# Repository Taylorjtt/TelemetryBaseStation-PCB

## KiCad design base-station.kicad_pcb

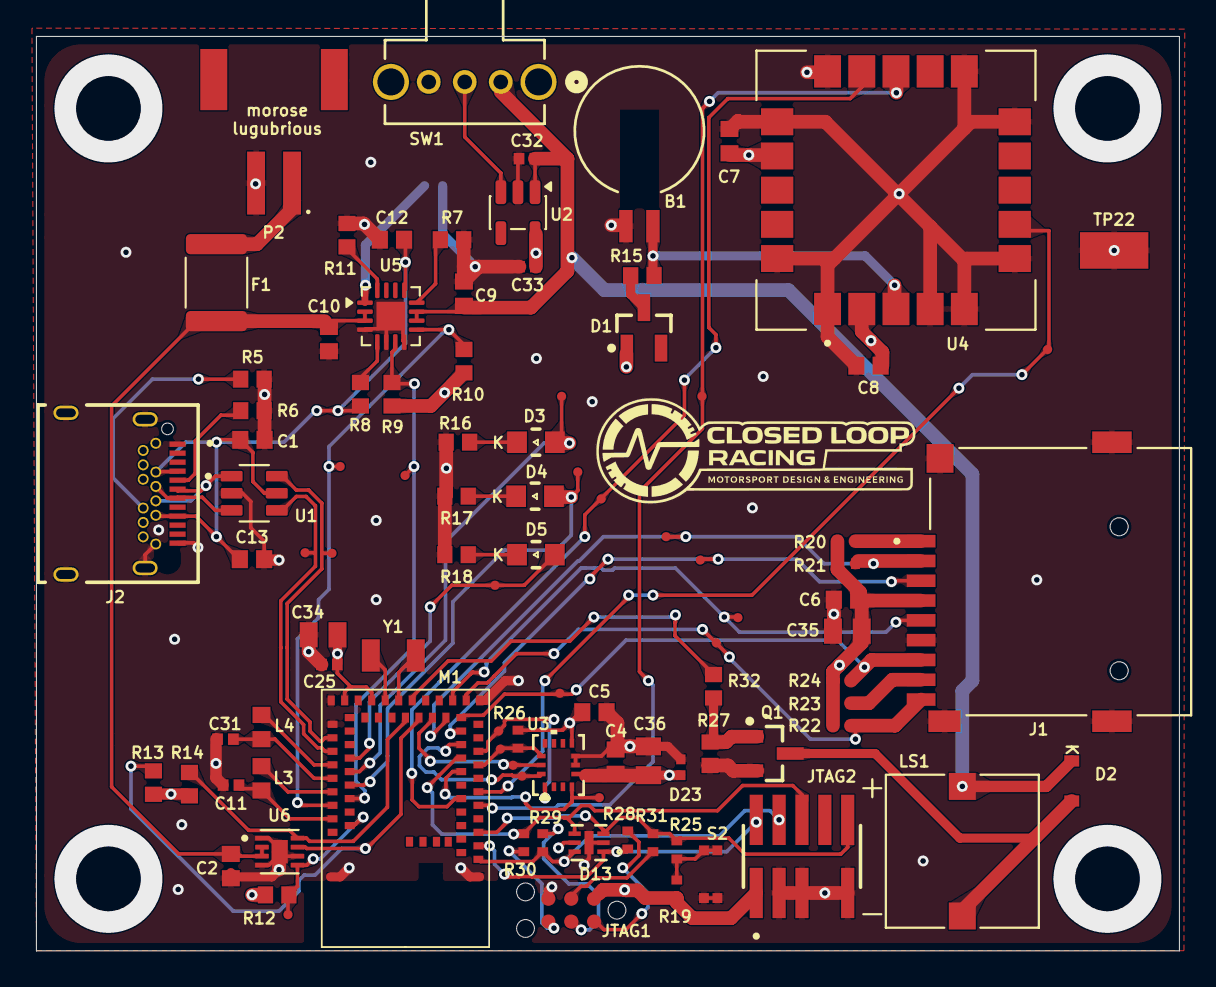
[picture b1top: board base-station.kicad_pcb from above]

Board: 4 copper layers, 63.5 x 50.8 mm, 98 parts (1 on the bottom side), 63 nets.

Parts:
B1: MS621FE-FL11E
C1, C2, C4, C5, C6, C7, C8, C13: 100nF; CAP 0603_1608
C9, C10, C12: 4.7uF; CAP 0603_1608
C11, C25, C31, C32, C33: 1uF; CAP 0402_1005
C34, C35, C36: 10uF; CAP 0805_2012
D1: SOT-23
D2: SOD323
D3: LED_0805_RED
D4: LED_0805_GREEN
D5: LED_0805_YELLOW
D13: SON6_DRTR5V0U4LP16-7_DIO
D23: DIODE 0402_1006
F1: Fuse_1812_4532Metric
J1: CUI_MSD-1-A
J2: GCT_USB4056-03-A_REVA2
JTAG1: TAG_CONNECT
JTAG2: SAMTEC_FTSH-105-01-L-DV-007-K
L3, L4: 10uH; IND 0603_1608
LS1: XDCR_SMT-0827-SW-3V-R
M1: MDBT53
P2: JST_S2B-PH-SM4-TB
Q1: SOT-23
R5, R6: 5.1k; RES 0603_1608
R7, R15, R16, R17, R18, R32: 1.1k; RES 0603_1608
R8, R9, R10, R12, R27: 100k; RES 0603_1608
R11: 887; RES 0603_1608
R13, R14: 4.7K; RES 0603_1608
R19, R20, R21, R22, R23, R24, R26: 10k; RES 0402_1005
R25, R28, R29, R30, R31: 150; RES 0402_1005
RT1: RES 0402_1005
S2: R-668048
SW1: OS102011MA1QN1_CNK
TP1, TP2, TP3, TP4, TP5, TP6, TP7, TP8, TP9, TP10, TP11, TP12, TP13, TP14, TP15, TP16, TP17, TP18, TP19, TP20, TP21: Testpoint_40mil
TP22: Testpoint
U1: SOT-23-6
U2: SOT-23-5
U3: BMI270_BOS
U4: XCVR_SAM-M10Q-00B
U5: VQFN-16-1EP_3x3mm_P0.5mm_EP1.6x1.6mm
U6: SON50P200X200X80-9N
Y1: 32.768 kHz; FC-135

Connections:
3.3V: C4.1, C5.1, C6.1, C7.1, C8.1, C25.1, C33.1, C34.1, C35.1, C36.2, D1.1 (A), D13.5, D23.1, J1.4 (VDD), JTAG1.1, JTAG2.01, M1.38 (VDD), M1.41 (VDDH), R9.1, R10.1, R12.1, R13.1, R14.1, R19.1, R20.1, R21.1, R22.1, R23.1, R24.1, R26.1, U2.5 (VOUT), U3.5 (VDDIO), U3.8 (VDD), U4.2 (V_IO), U4.17 (VCC)
+BATT: C2.1, C10.1, F1.1, U5.2 (BAT), U5.3 (BAT), U6.2 (CELL), U6.3 (VDD)
/ALERT: M1.59 (P1.10), R12.2, TP21.1 (1_1), U6.5 (~ALERT)
/BMI_CS: M1.16 (P0.18/QSPI_CSN), R26.2, TP5.1 (1_1), U3.12 (CSB)
/BMI_MISO: M1.18 (P0.10/HSPI_MISO), TP6.1 (1_1), U3.1 (SDO)
/BMI_MOSI: M1.19 (P0.09/HSPI_MOSI), TP7.1 (1_1), U3.14 (SDX)
/BMI_SCK: M1.29 (P0.08/HSPI_SCK), TP13.1 (1_1), U3.13 (SCX)
/BUZZER: M1.32 (P0.02/NFC1), R32.1
/CARD_DETECT: J1.CD, M1.25 (P0.22), R22.2, TP10.1 (1_1)
/CHG: M1.56 (P0.31), R10.2, TP20.1 (1_1), U5.9 (~CHG)
/D+: M1.46 (D+), TP14.1 (1_1), U1.6
/D-: M1.48 (D-), TP15.1 (1_1), U1.4
/Din+: J2.A6 (DP1), J2.B6 (DP2), U1.1
/Din-: J2.A7 (DN1), J2.B7 (DN2), U1.3
/GPS_LOCK: D3.2, M1.51 (P1.13), TP17.1 (1_1)
/INT1: M1.15 (P0.12/HSPI_DCX), TP4.1 (1_1), U3.4 (INT1)
/PGOOD: M1.55 (P1.11), R9.2, TP19.1 (1_1), U5.7 (~PGOOD)
/RADIO_LINK: D5.2, M1.49 (P1.14), TP16.1 (1_1)
/RECORD: D4.2, M1.53 (P1.12), TP18.1 (1_1)
/RESET: D13.3, JTAG2.10, M1.6 (~RESET), R25.2, R31.1
/SCL: M1.31 (P1.03/TWI), R13.2, U6.7 (SCL)
/SDA: M1.33 (P1.02/TWI), R14.2, U6.8 (SDA)
/SD_CLK: J1.5 (CLK), M1.26 (P0.17/QSPI_SCK), TP11.1 (1_1)
/SD_CS: J1.2 (CD/DAT3), M1.27 (P0.14/QSPI1), R21.2, TP12.1 (1_1)
/SD_MISO: J1.7 (DAT0), M1.23 (P0.15/QSPI2), R24.2, TP9.1 (1_1)
/SD_MOSI: J1.3 (CMD), M1.21 (P0.13/QSPI0), TP8.1 (1_1)
/SWCLK: D13.6, JTAG2.04, M1.2 (SWDCLK), R29.2
/SWDIO: D13.1, JTAG2.02, M1.4 (SWDIO), R28.1
/SWITCH: SW1.2, U2.3 (EN)
/SWO: D13.4, JTAG2.06, M1.17 (P0.11/HSPI_CSN), R30.1
/TIMEPULSE: M1.12 (P0.21), TP3.1 (1_1), U4.7 (TIMEPULSE)
/TS: RT1.2, U5.1 (TS)
/UART_RX: M1.10 (P1.06), TP1.1 (1_1), U4.13 (TXD)
/UART_TX: M1.11 (P1.04), TP2.1 (1_1), U4.14 (RXD)
/V_BCKP: B1.1 (+), R15.1, U4.3 (V_BCKP)
GND: B1.2 (-), C1.2, C2.2, C4.2, C5.2, C6.2, C7.2, C8.2, C9.1, C10.2, C11.2, C12.1, C13.2, C25.2, C31.2, C32.2, C33.2, C34.2, C35.2, C36.1, D13.2, D13.7 (Pad), D23.2, J1.6 (VSS), J1.G1 (COVER_GND), J1.G2 (COVER_GND__1), J1.G3 (COVER_GND__2), J1.G4 (COVER_GND__3), J2.A1 (GND_A), J2.A12 (GND_A__1), J2.B1 (GND_B), J2.B12 (GND_B__1), J2.S1 (SHELL_GND), J2.S2 (SHELL_GND__1), J2.S3 (SHELL_GND__2), J2.S4 (SHELL_GND__3), JTAG1.5, JTAG2.03, JTAG2.05, JTAG2.09, M1.1 (GND), M1.24 (GND), M1.42 (GND), M1.44 (VBUS), M1.61 (GND), P2.2, Q1.2, R5.2, R6.1, R7.2, R11.2, R16.2, R17.2, R18.2, R27.1, RT1.1, S2.1, SW1.3, TP22.1 (1_1), U1.2, U2.2 (GND), U3.6 (GNDIO), U3.7 (GND), U4.1 (GND), U4.4 (GND), U4.5 (GND), U4.6 (GND), U4.10 (GND), U4.11 (GND), U4.15 (GND), U4.16 (GND), U4.20 (GND), U5.4 (~CE), U5.6 (EN1), U5.8 (VSS), U5.17 (VSS), U6.1 (CTG), U6.4 (GND), U6.6 (QSTRT), U6.9 (EP)
unnamed: D1.3 (K), R15.2
unnamed: D2.2 (A), LS1.N, Q1.3
unnamed: D3.1, R16.1
unnamed: D4.1, R17.1
unnamed: D5.1, R18.1
unnamed: F1.2, P2.1
unnamed: J1.8 (DAT1), R23.2
unnamed: J1.1 (DAT2), R20.2
unnamed: J2.A5 (CC1), R6.2
unnamed: J2.B5 (CC2), R5.1
unnamed: JTAG1.2, R28.2
unnamed: JTAG1.3, R31.2
unnamed: JTAG1.4, R29.1
unnamed: JTAG1.6, R30.2
unnamed: L3.1, M1.54 (DCC)
unnamed: L4.1, M1.50 (DCCD)
unnamed: C31.1, L4.2, M1.52 (DECD)
unnamed: C11.1, L3.2, M1.58 (DECR)
unnamed: M1.34 (P0.00/XL1), Y1.1
unnamed: M1.36 (P0.01/XL2), Y1.3
unnamed: Q1.1, R27.2, R32.2
unnamed: R19.2, R25.1, S2.2
unnamed: R8.2, U5.5 (EN2)
unnamed: R7.1, U5.12 (ILIM)
unnamed: R11.1, U5.16 (ISET)
VBUS: C1.1, C12.2, C13.1, J2.A4 (VBUS_A), J2.A9 (VBUS_A__1), J2.B4 (VBUS_B), J2.B9 (VBUS_B__1), R8.1, U1.5, U5.13 (IN)
VOut: C9.2, C32.1, D2.1 (C), LS1.P, SW1.1, U2.1 (VIN), U5.10 (OUT), U5.11 (OUT)

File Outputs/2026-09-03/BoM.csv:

"#","Description","Reference","Value","Footprint","Qty","Datasheet","MANUFACTURER","MANUFACTURER PART NUMBER"
"1","BATT LITHIUM 3V 5.5MAH COIN","B1","","base-station:MS621FE-FL11E","1","https://www.sii.co.jp/hubfs/40217095/MicroBattery_E_20230330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","Seiko Instruments","MS621FE-FL11E"
"2","CAP CER 0.1UF 10V X5R 0603","C1,C2,C4,C5,C6,C7,C8,C13","100nF","base-station:CAP 0603_1608","8","https://datasheets.kyocera-avx.com/cx5r.pdf","KYOCERA AVX","0603ZD104KAT2A"
"3","CAP CER 4.7UF 16V X5R 0603","C9,C10,C12","4.7uF","base-station:CAP 0603_1608","3","https://mm.digikey.com/Volume0/opasdata/d220001/medias/docus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","Samsung Electro-Mechanics","CL10A475KO8NNNC"
"4","CAP CER 1UF 6.3V X7R 0402","C11,C25,C31,C32,C33","1uF","base-station:CAP 0402_1005","5","https://search.murata.co.jp/Ceramy/image/img/A01X/G101/ENG/G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","Murata Electronics","GRM155R70J105KA12J"
"5","CAP CER 10UF 10V X7R 0805","C34,C35,C36","10uF","base-station:CAP 0805_2012","3","https://search.murata.co.jp/Ceramy/image/img/A01X/G101/ENG/G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","Murata Electronics","GRM21BR71A106KA73L"
"6","DIODE SCHOTTKY 30V 200MA SOT23-3","D1","","base-station:SOT-23","1","https://diotec.com/request/datasheet/bat54.pdf","Diotec Semiconductor","BAT54"
"7","DIODE STANDARD 75V 150MA SOD323F","D2","","base-station:SOD323","1","https://www.onsemi.com/pub/Collateral/1N4148WS-D.PDF","onsemi","1N4148WS"
"8","LED RED CLEAR 0805 SMD","D3","","base-station:LED_0805_RED","1","https://www.we-online.com/components/products/datasheet/1500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","Würth Elektronik","150080RS75000"
"9","LED GREEN CLEAR 0805 SMD","D4","","base-station:LED_0805_GREEN","1","https://www.we-online.com/components/products/datasheet/1500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","Würth Elektronik","150080GS75000"
"10","LED YELLOW CLEAR 0805 SMD","D5","","base-station:LED_0805_YELLOW","1","https://www.we-online.com/components/products/datasheet/1500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","Würth Elektronik","150080YS75000"
"11","TVS DIODE 5.5VWM 12V U-DFN1616-6","D13","","base-station:SON6_DRTR5V0U4LP16-7_DIO","1","https://www.diodes.com/assets/Datasheets/DRTR5V0U4LP16.pdf","Diodes Incorporated","DRTR5V0U4LP16-7"
"12","TVS DIODE 5.5VWM 12.5VC 2DFN","D23","","base-station:DIODE 0402_1006","1","https://www.diodes.com/assets/Datasheets/D5V0H1B2LP.pdf","Diodes Incorporated","D5V0H1B2LP-7B"
"13","PTC RESET FUSE 15V 500MA 1812","F1","","base-station:Fuse_1812_4532Metric","1","https://www.bourns.com/docs/product-datasheets/mf-msmf.pdf","Bourns Inc.","MF-MSMF050-2"
"14","CONN MICROSD CARD R/A SMD","J1","","base-station:CUI_MSD-1-A","1","https://www.cuidevices.com/product/resource/digikeypdf/msd-1-a.pdf","Same Sky (Formerly CUI Devices)","MSD-1-A"
"15","USB C 3.2 REC, HORZ, HYBRID PCB","J2","","base-station:GCT_USB4056-03-A_REVA2","1","https://gct.co/files/specs/usb4056-spec.pdf","GCT","USB4056-03-A"
"16","CONN HEADER SMD 10POS 1.27MM","JTAG2","","base-station:SAMTEC_FTSH-105-01-L-DV-007-K","1","https://suddendocs.samtec.com/catalog_english/ftsh_smt.pdf","Samtec Inc.","FTSH-105-01-L-DV-007-K"
"17","FIXED IND 10UH 250MA 1.05OHM SMD","L3,L4","10uH","base-station:IND 0603_1608","2","https://product.tdk.com/en/system/files/dam/doc/product/indu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","TDK Corporation","MLZ1608M100WTD25"
"18","BUZZER MAGNETIC 3.6V 0.3X0.3 SMD","LS1","","base-station:XDCR_SMT-0827-SW-3V-R","1","https://puiaudio.com/file/specs-SMT-0827-SW-3V-R.pdf","Pui Audio","SMT-0827-SW-3V-R"
"19","RF TXRX MOD 802.15.4 BT U.FL SMD","M1","","base-station:MDBT53","1","https://www.raytac.com/download/index.php?index_id=61","Raytac","MDBT53-U1M"
"20","CONN HEADER SMD R/A 2POS 2MM","P2","","base-station:JST_S2B-PH-SM4-TB","1","https://www.jst-mfg.com/product/pdf/eng/ePH.pdf","JST","S2B-PH-SM4-TB"
"21","MOSFET N-CH 30V 5.7A SOT23-3L","Q1","","base-station:SOT-23","1","https://mm.digikey.com/Volume0/opasdata/d220001/medias/docus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","Alpha & Omega Semiconductor","AO3400A"
"22","RES 5.1K OHM 1% 1/10W 0603","R5,R6","5.1k","base-station:RES 0603_1608","2","https://www.seielect.com/catalog/SEI-RMCF_RMCP.pdf","Stackpole Electronics Inc","RMCF0603FT5K10"
"23","RES 1.1K OHM 1% 1/10W 0603","R7,R15,R16,R17,R18,R32","1.1k","base-station:RES 0603_1608","6","https://www.seielect.com/catalog/SEI-RMCF_RMCP.pdf","Stackpole Electronics Inc","RMCF0603FT1K10"
"24","RES 100K OHM 1% 1/10W 0603","R8,R9,R10,R12,R27","100k","base-station:RES 0603_1608","5","https://www.seielect.com/catalog/SEI-RMCF_RMCP.pdf","Stackpole Electronics Inc","RMCF0603FG100K"
"25","RES 887 OHM 1% 1/10W 0603","R11","887","base-station:RES 0603_1608","1","https://www.seielect.com/catalog/SEI-RMCF_RMCP.pdf","Stackpole Electronics Inc","RMCF0603FT887R"
"26","RES 4.7K OHM 1% 1/10W 0603","R13,R14","4.7K","base-station:RES 0603_1608","2","https://www.seielect.com/catalog/SEI-RMCF_RMCP.pdf","Stackpole Electronics Inc","RMCF0603FT4K70"
"27","RES SMD 10K OHM 1% 1/10W 0402","R19,R20,R21,R22,R23,R24,R26","10k","base-station:RES 0402_1005","7","https://industrial.panasonic.com/cdbs/www-data/pdf/RDA0000/A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","Panasonic Electronic Components","ERJ-2RKF1002X"
"28","RES SMD 150 OHM 1% 1/10W 0402","R25,R28,R29,R30,R31","150","base-station:RES 0402_1005","5","https://industrial.panasonic.com/cdbs/www-data/pdf/RDA0000/A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","Panasonic Electronic Components","ERJ-2RKF1500X"
"29","THERMISTOR NTC 10KOHM 3380K 0402","RT1","","base-station:RES 0402_1005","1","https://mm.digikey.com/Volume0/opasdata/d220001/medias/docus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","Murata Electronics","NCP15XH103F03RC"
"30","SWITCH TACTILE SPST-NO 0.02A 15V","S2","","base-station:R-668048","1","https://mm.digikey.com/Volume0/opasdata/d220001/medias/docus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","Mitsumi Electric Company Ltd","R-668048"
"31","SWITCH SLIDE SPDT 100MA 12V","SW1","","base-station:OS102011MA1QN1_CNK","1","https://www.littelfuse.com/assetdocs/littelfuse-c-k-slide-os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","C&K","OS102011MA1QN1"
"32","13V Clamp 6A (8/20µs) Ipp Tvs Diode Surface Mount SOT-23-6","U1","","base-station:SOT-23-6","1","https://mm.digikey.com/Volume0/opasdata/d220001/medias/docus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","Shenzhen Slkormicro Semicon Co., Ltd.","USBLC6-2SC6"
"33","IC REG LINEAR 3.3V 600MA SOT-25","U2","","base-station:SOT-23-5","1","https://www.diodes.com/assets/Datasheets/AP2112.pdf","Diodes Incorporated","AP2112K-3.3TRG1"
"34","IMU ACCEL/GYRO I2C/SPI 14LGA","U3","","base-station:BMI270_BOS","1","https://www.bosch-sensortec.com/media/boschsensortec/downloa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","Bosch Sensortec","BMI270"
"35","M10 GNSS LGA PATCH ANTENNA MOD","U4","","base-station:XCVR_SAM-M10Q-00B","1","https://content.u-blox.com/sites/default/files/documents/SAM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","u-blox","SAM-M10Q-00B"
"36","USB-Friendly Li-Ion Battery Charger and Power-Path Management, VQFN-16","U5","","base-station:VQFN-16-1EP_3x3mm_P0.5mm_EP1.6x1.6mm","1","http://www.ti.com/lit/ds/symlink/bq24074.pdf","Texas Instruments","BQ24074RGT"
"37","IC BATT MON LI-ION 1CELL 8TDFN","U6","","base-station:SON50P200X200X80-9N","1","https://www.analog.com/media/en/technical-documentation/data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","Analog Devices Inc./Maxim Integrated","MAX17048G+T10"
"38","CRYSTAL 32.7680KHZ 9PF SMD","Y1","32.768 kHz","base-station:FC-135","1","https://www.we-online.com/components/products/datasheet/8300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","Wurth Elektronik","830009706"

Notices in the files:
parts and their libraries:
License: Apache-2.0
